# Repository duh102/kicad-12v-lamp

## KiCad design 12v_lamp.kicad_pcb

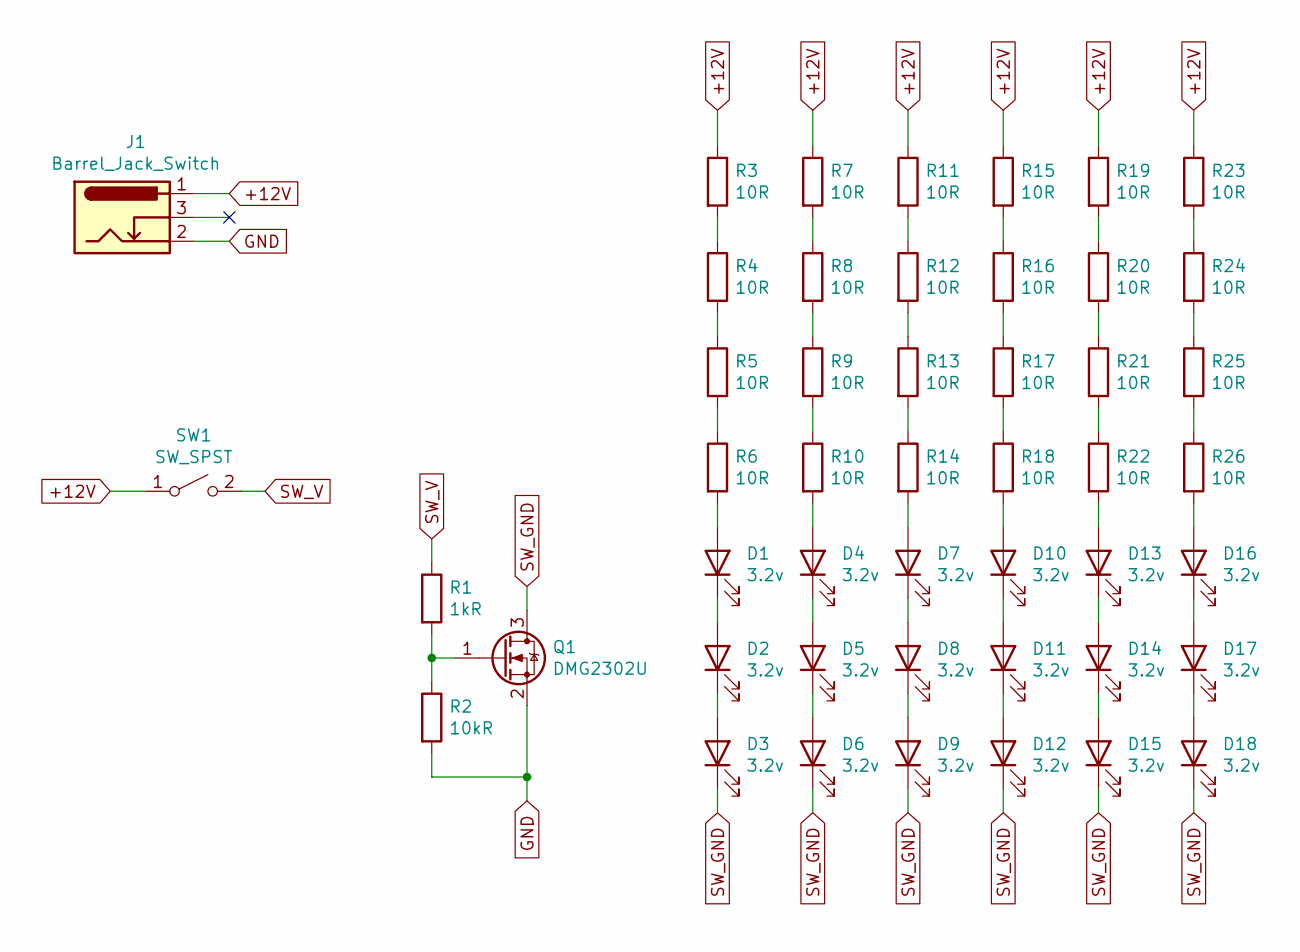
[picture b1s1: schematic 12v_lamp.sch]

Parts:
D1, D2, D3, D4, D5, D6, D7, D8, D9, D10, D11, D12, D13, D14, D15, D16, D17, D18: 3.2v; LED_Yuji_5730
J1: Barrel_Jack_Switch; Barrel_Jack_Tensility_54-00167_5.5mmOD_2.5mmID
Q1: DMG2302U; SOT-23
R1: 1kR; R_0805_2012Metric
R2: 10kR; R_0805_2012Metric
R3, R4, R5, R6, R7, R8, R9, R10, R11, R12, R13, R14, R15, R16, R17, R18, R19, R20, R21, R22, R23, R24, R25, R26: 10R; R_0805_2012Metric
SW1: SW_SPST; PinHeader_1x02_P2.54mm_Vertical

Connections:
+12V: J1.1, R3.1, R7.1, R11.1, R15.1, R19.1, R23.1, SW1.1 (A)
GND: J1.2, Q1.2 (S), R2.2
unnamed: D1.1 (K), D2.2 (A)
unnamed: D1.2 (A), R6.2
unnamed: D2.1 (K), D3.2 (A)
unnamed: D4.1 (K), D5.2 (A)
unnamed: D4.2 (A), R10.2
unnamed: D5.1 (K), D6.2 (A)
unnamed: D7.1 (K), D8.2 (A)
unnamed: D7.2 (A), R14.2
unnamed: D8.1 (K), D9.2 (A)
unnamed: D10.1 (K), D11.2 (A)
unnamed: D10.2 (A), R18.2
unnamed: D11.1 (K), D12.2 (A)
unnamed: D13.1 (K), D14.2 (A)
unnamed: D13.2 (A), R22.2
unnamed: D14.1 (K), D15.2 (A)
unnamed: D16.1 (K), D17.2 (A)
unnamed: D16.2 (A), R26.2
unnamed: D17.1 (K), D18.2 (A)
unnamed: Q1.1 (G), R1.2, R2.1
unnamed: R3.2, R4.1
unnamed: R4.2, R5.1
unnamed: R5.2, R6.1
unnamed: R7.2, R8.1
unnamed: R8.2, R9.1
unnamed: R9.2, R10.1
unnamed: R11.2, R12.1
unnamed: R12.2, R13.1
unnamed: R13.2, R14.1
unnamed: R15.2, R16.1
unnamed: R16.2, R17.1
unnamed: R17.2, R18.1
unnamed: R19.2, R20.1
unnamed: R20.2, R21.1
unnamed: R21.2, R22.1
unnamed: R23.2, R24.1
unnamed: R24.2, R25.1
unnamed: R25.2, R26.1
SW_GND: D3.1 (K), D6.1 (K), D9.1 (K), D12.1 (K), D15.1 (K), D18.1 (K), Q1.3 (D)
SW_V: R1.1, SW1.2 (B)

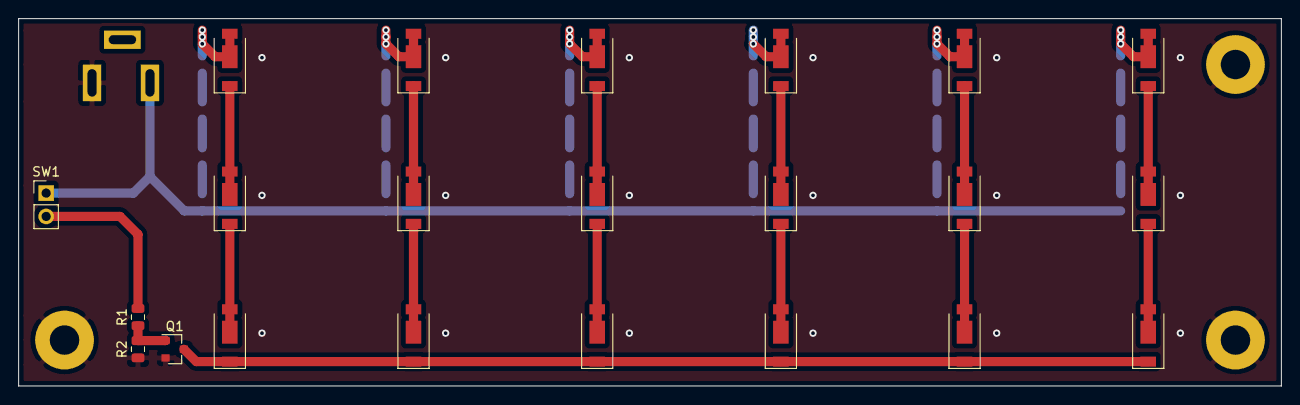
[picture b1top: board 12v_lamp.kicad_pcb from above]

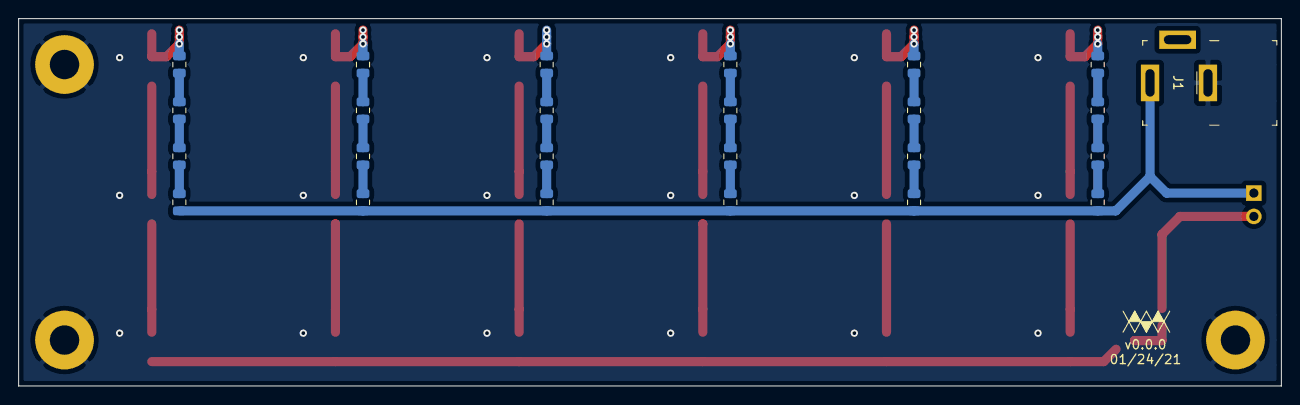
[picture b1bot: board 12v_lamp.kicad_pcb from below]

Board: 2 copper layers, 137.5 x 40.0 mm, 47 parts (25 on the bottom side), 41 nets.

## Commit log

2021-01-25 Add logo
